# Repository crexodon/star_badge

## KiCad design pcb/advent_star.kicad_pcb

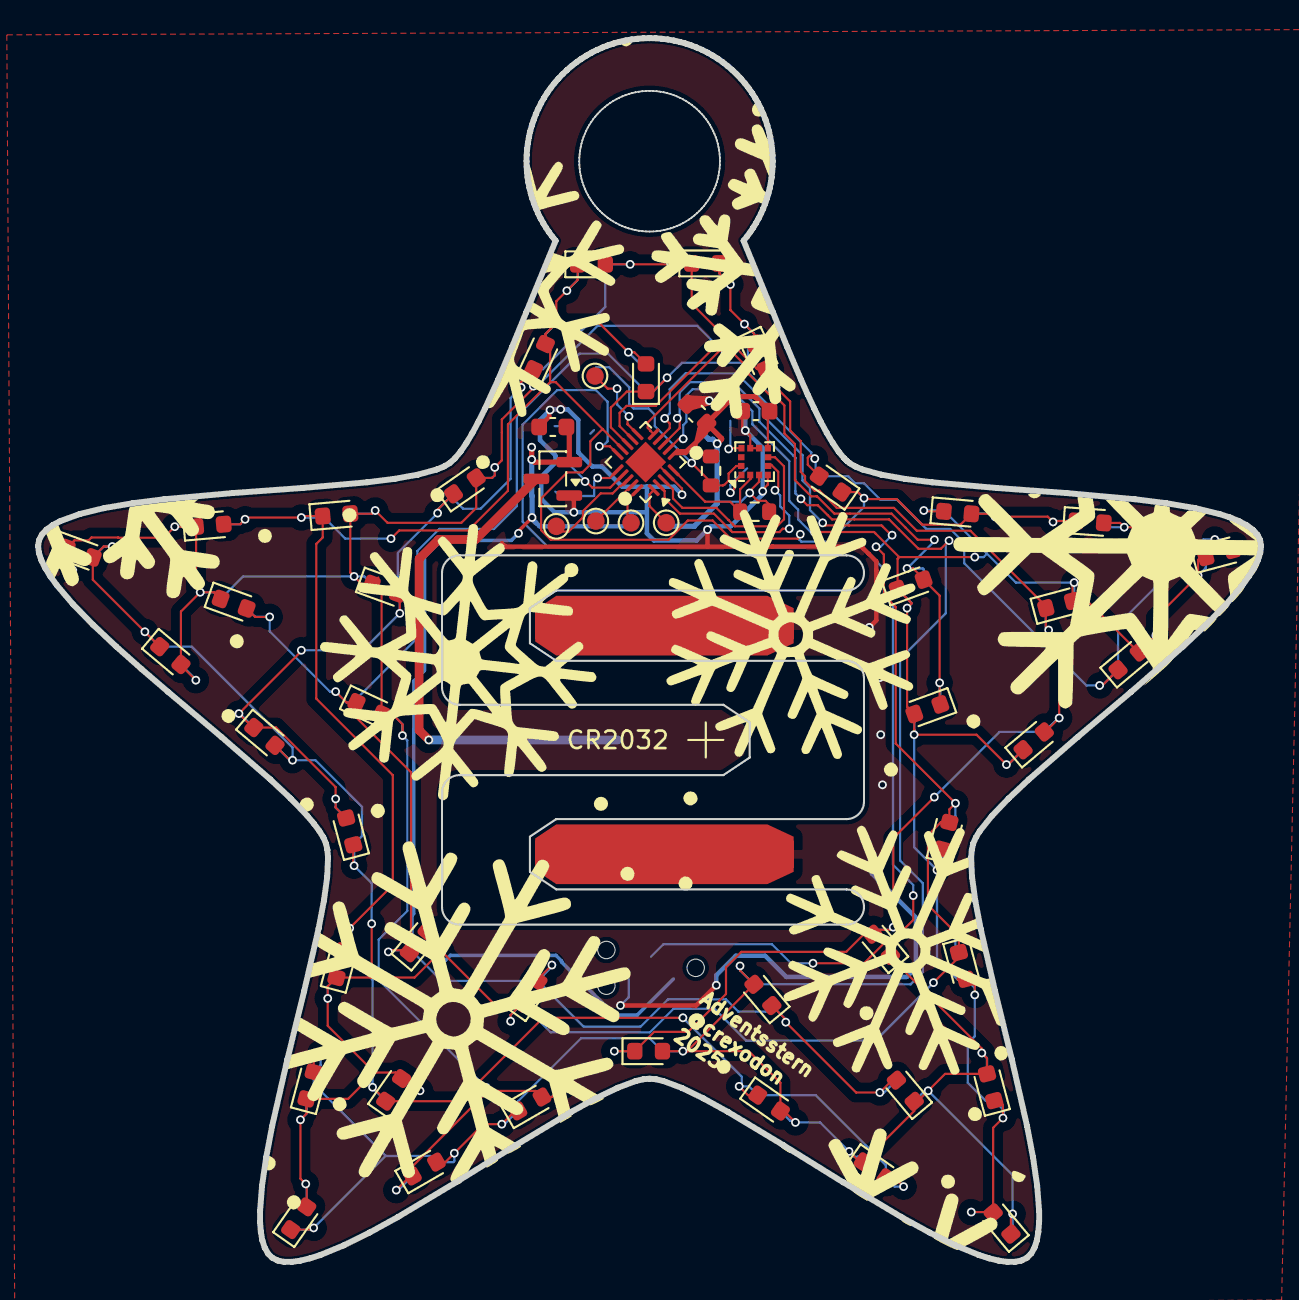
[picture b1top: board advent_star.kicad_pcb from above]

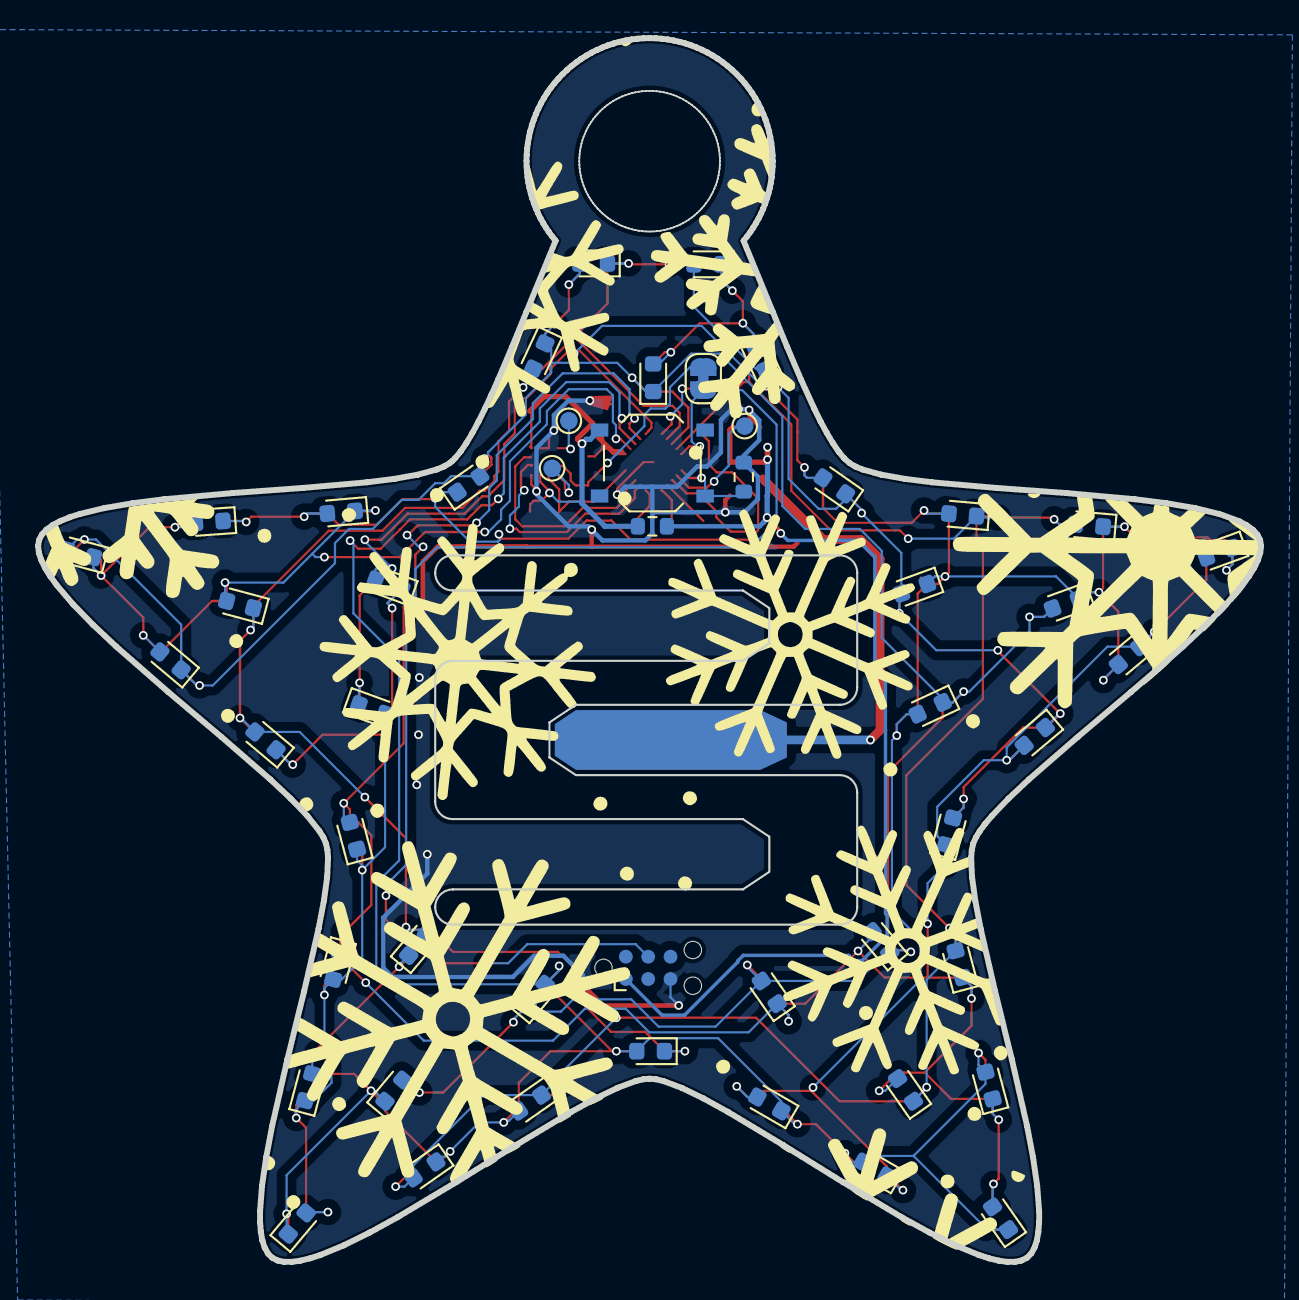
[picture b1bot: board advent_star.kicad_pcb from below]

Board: 2 copper layers, 69.6 x 69.6 mm, 106 parts (50 on the bottom side), 24 nets.

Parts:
BT1: CR2032; CR2032_PCBcutout
C1: 47u; C_0603_1608Metric
C2, C3: 100n; C_0603_1608Metric
D1, D2, D3, D4, D5, D6, D7, D8, D9, D10, D11, D12, D13, D14, D15, D16, D17, D18, D19, D20, D21, D22, D23, D24, D25, D26, D27, D28, D29, D30, D31, D32, D33, D34, D35, D36, D37, D38, D39, D40, D41, D42, D43, D44, D45, D46, D47, D48, D49, D50, D51, D52, D53, D54, D55, D56, D57, D58, D59, D60, D61, D62, D63, D64, D65, D66, D67, D68, D69, D70, D71, D72, D73, D74, D75, D76, D77, D78, D79, D80, D81, D82, D83, D84: LED; LED_0603_1608Metric
J1: TC2030; Tag-Connect_TC2030-IDC-NL_2x03_P1.27mm_Vertical
JP1: SolderJumper_2_Bridged; SolderJumper-2_P1.3mm_Bridged_RoundedPad1.0x1.5mm
Q1: AO3401A; SOT-23
R1: 10k; R_0603_1608Metric
R2, R3: 2k2; R_0603_1608Metric
R4: 0; R_0603_1608Metric
SW1: SW_Push_Dual; SW_Push_1P1T_XKB_TS-1187A
TP1, TP2, TP3, TP4, TP5, TP7, TP8, TP9: TestPoint_Small; TestPoint_Pad_D1.0mm
U1: CH32V003FxUx; QFN-20-1EP_3x3mm_P0.4mm_EP1.65x1.65mm
U2: SC7A20; LGA-12_2x2mm_P0.5mm

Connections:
+BATT: BT1.1 (+), Q1.3 (D)
GND: BT1.2 (-), C1.2, C2.2, C3.2, J1.5, Q1.1 (G), R1.2, U1.4 (VSS), U1.21 (VSS), U2.4 (NC), U2.8 (GNDIO), U2.9 (GND)
INT1: U1.2 (PA1), U2.5 (INT1)
INT2: U1.3 (PA2), U2.6 (INT2)
LED_C1: D1.1 (K), D2.1 (K), D3.2 (A), D4.2 (A), D5.1 (K), D6.1 (K), D7.2 (A), D8.2 (A), D9.1 (K), D10.1 (K), D11.2 (A), D12.2 (A), D13.1 (K), D14.1 (K), D15.2 (A), D16.2 (A), D17.1 (K), D18.1 (K), D19.2 (A), D20.2 (A), D21.1 (K), D22.1 (K), D23.2 (A), D24.2 (A), U1.7 (PC0)
LED_C2: D21.2 (A), D22.2 (A), D23.1 (K), D24.1 (K), D25.1 (K), D26.1 (K), D27.2 (A), D28.2 (A), D29.1 (K), D30.1 (K), D31.2 (A), D32.2 (A), D33.1 (K), D34.1 (K), D35.2 (A), D36.2 (A), D37.1 (K), D38.1 (K), D39.2 (A), D40.2 (A), D41.1 (K), D42.1 (K), D43.2 (A), D44.2 (A), U1.8 (PC1)
LED_C3: D17.2 (A), D18.2 (A), D19.1 (K), D20.1 (K), D41.2 (A), D42.2 (A), D43.1 (K), D44.1 (K), D45.1 (K), D46.1 (K), D47.2 (A), D48.2 (A), D49.1 (K), D50.1 (K), D51.2 (A), D52.2 (A), D53.1 (K), D54.1 (K), D55.2 (A), D56.2 (A), D57.1 (K), D58.1 (K), D59.2 (A), D60.2 (A), U1.9 (PC2)
LED_C4: D13.2 (A), D14.2 (A), D15.1 (K), D16.1 (K), D37.2 (A), D38.2 (A), D39.1 (K), D40.1 (K), D57.2 (A), D58.2 (A), D59.1 (K), D60.1 (K), D61.1 (K), D62.1 (K), D63.2 (A), D64.2 (A), D65.1 (K), D66.1 (K), D67.2 (A), D68.2 (A), D69.1 (K), D70.1 (K), D71.2 (A), D72.2 (A), U1.10 (PC3)
LED_C5: D9.2 (A), D10.2 (A), D11.1 (K), D12.1 (K), D33.2 (A), D34.2 (A), D35.1 (K), D36.1 (K), D53.2 (A), D54.2 (A), D55.1 (K), D56.1 (K), D69.2 (A), D70.2 (A), D71.1 (K), D72.1 (K), D73.1 (K), D74.1 (K), D75.2 (A), D76.2 (A), D77.1 (K), D78.1 (K), D79.2 (A), D80.2 (A), U1.12 (PC5)
LED_C6: D5.2 (A), D6.2 (A), D7.1 (K), D8.1 (K), D29.2 (A), D30.2 (A), D31.1 (K), D32.1 (K), D49.2 (A), D50.2 (A), D51.1 (K), D52.1 (K), D65.2 (A), D66.2 (A), D67.1 (K), D68.1 (K), D77.2 (A), D78.2 (A), D79.1 (K), D80.1 (K), D81.1 (K), D82.1 (K), D83.2 (A), D84.2 (A), U1.13 (PC6)
LED_C7: D1.2 (A), D2.2 (A), D3.1 (K), D4.1 (K), D25.2 (A), D26.2 (A), D27.1 (K), D28.1 (K), D45.2 (A), D46.2 (A), D47.1 (K), D48.1 (K), D61.2 (A), D62.2 (A), D63.1 (K), D64.1 (K), D73.2 (A), D74.2 (A), D75.1 (K), D76.1 (K), D81.2 (A), D82.2 (A), D83.1 (K), D84.1 (K), U1.14 (PC7)
unnamed: TP9.1, U1.11 (PC4)
unnamed: TP1.1, U1.17 (PD3)
unnamed: TP2.1, U1.18 (PD4)
unnamed: TP3.1, U1.19 (PD5)
unnamed: TP4.1, U1.20 (PD6)
unnamed: TP5.1, U1.1 (PD7)
unnamed: TP8.1, U2.1 (SDO)
unnamed: TP7.1, U2.10 (~CS)
SCL: JP1.2 (B), R2.2, U2.12 (SCx)
SDA: R3.2, U1.5 (PD0), U2.2 (SDx)
SWIO: J1.4, JP1.1 (A), U1.15 (PD1)
USER_BTN: R1.1, SW1.1, U1.16 (PD2)
VDD: C1.1, C2.1, C3.1, J1.1, Q1.2 (S), R2.1, R3.1, R4.1, R4.2, SW1.2, U1.6 (VDD), U2.3 (VDDIO), U2.7 (VDD)

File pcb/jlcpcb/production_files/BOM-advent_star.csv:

Comment,Designator,Footprint,LCSC,Quantity
0,R4,R_0603_1608Metric,C21189,1
100n,"C2,C3",C_0603_1608Metric,C14663,2
10k,R1,R_0603_1608Metric,C25197,1
2k2,"R2,R3",R_0603_1608Metric,C4190,2
47u,C1,C_0603_1608Metric,C59461,1
AO3401A,Q1,SOT-23,C15127,1
CH32V003FxUx,U1,QFN-20-1EP_3x3mm_P0.4mm_EP1.65x1.65mm,C5299908,1
LED,"D1,D10,D11,D12,D13,D14,D15,D16,D17,D18,D19,D2,D20,D21,D22,D23,D24,D25,D26,D27,D28,D29,D3,D30,D31,D32,D33,D34,D35,D36,D37,D38,D39,D4,D40,D41,D42,D43,D44,D45,D46,D47,D48,D49,D5,D50,D51,D52,D53,D54,D55,D56,D57,D58,D59,D6,D60,D61,D62,D63,D64,D65,D66,D67,D68,D69,D7,D70,D71,D72,D73,D74,D75,D76,D77,D78,D79,D8,D80,D81,D82,D83,D84,D9",LED_0603_1608Metric,C2837383,84
SC7A20,U2,LGA-12_2x2mm_P0.5mm,C5126709,1
SW_Push_Dual,SW1,SW_Push_1P1T_XKB_TS-1187A,C318884,1

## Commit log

2025-11-09 initial commit with schematic done. Layout is WIP
2025-11-10 changed pin mapping of I2C, all LED pins are now on a 'high current capable' pin
2025-11-12 charlieplex matrix finished, WIP on routing microcontroller
2025-11-13 almost done with routing, needs two ground pads to be connected
2025-11-13 finished assignment of parts for jlcpcb, current state is ordered
2025-11-19 init firmware
2025-11-26 Added wlink for upload and startup file (default currently)
2025-11-26 Added charlie matrix, works with a test function, proper animations are WIP
2025-11-26 Added multiplexing mode and needed "fast pwm" for the charliematrix. Added all into a test function to test the star
2025-11-26 Added simple animations
2025-11-26 Added nice animations, but still WIP. They don't produce the expected output!
